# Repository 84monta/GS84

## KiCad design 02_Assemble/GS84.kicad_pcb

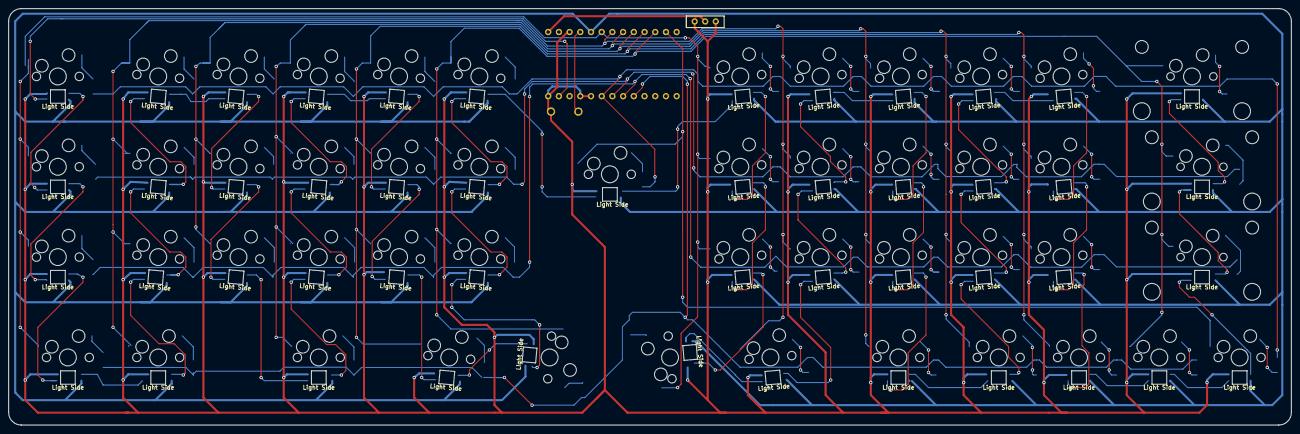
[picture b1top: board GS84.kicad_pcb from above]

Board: 2 copper layers, 304.4 x 98.8 mm, 150 parts (0 on the bottom side), 113 nets.

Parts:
D1, D2, D3, D4, D5, D6, D7, D8, D9, D10, D11, D12, D13, D14, D15, D16, D17, D18, D19, D20, D21, D22, D23, D24, D25, D26, D27, D28, D29, D30, D31, D32, D33, D34, D35, D36, D37, D38, D39, D40, D41, D42, D43, D44, D45, D46, D47, D48, D49: D; Diode_SMD
J1: Conn_01x02; Battery_XH2.5_GL_PCB
L1, L2, L3, L4, L5, L6, L7, L8, L9, L10, L11, L12, L13, L14, L15, L16, L17, L18, L19, L20, L21, L22, L23, L24, L25, L26, L27, L28, L29, L30, L31, L32, L33, L34, L35, L36, L37, L38, L39, L40, L41, L42, L43, L44, L45, L46, L47, L48, L49: SK6812MINI; LED_SK6812MINI-E_BL
SW1, SW2, SW3, SW19, SW23, SW28, SW32: SW_PUSH; CherryMX_Hotswap_1.25u
SW4, SW5, SW6, SW7, SW8, SW9, SW10, SW11, SW12, SW13, SW14, SW15, SW16, SW17, SW18, SW20, SW21, SW22, SW25, SW26, SW27, SW29, SW30, SW31, SW33, SW34, SW35, SW36, SW37, SW38, SW39, SW40, SW41, SW42, SW43, SW44, SW48, SW49: SW_PUSH; CherryMX_Hotswap_1u
SW24: SW_PUSH; CherryMX_Hotswap_1u_Small1
SW45: SW_PUSH; CherryMX_Hotswap_2u
SW46, SW47: SW_PUSH; CherryMX_Hotswap_2.25u
SW50: SW_PUSH; ResetSW
U1: BLEMicroPro; Micon_BMP_GL

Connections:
Bat+: J1.1, U1.25
Col0: SW1.1, SW2.1, SW3.1, SW4.1, SW25.1, SW26.1, SW27.1, SW28.1, U1.20
Col1: SW5.1, SW6.1, SW7.1, SW8.1, SW29.1, SW30.1, SW31.1, SW32.1, U1.19
Col2: SW9.1, SW10.1, SW11.1, SW33.1, SW34.1, SW35.1, SW36.1, U1.18
Col3: SW12.1, SW13.1, SW14.1, SW15.1, SW37.1, SW38.1, SW39.1, SW40.1, U1.17
Col4: SW16.1, SW17.1, SW18.1, SW19.1, SW41.1, SW42.1, SW43.1, SW44.1, U1.16
Col5: SW20.1, SW21.1, SW22.1, SW23.1, SW45.1, SW46.1, SW47.1, SW48.1, U1.15
Col6: SW24.1, SW49.1, U1.14
GND: J1.2, L1.2, L2.2, L3.2, L4.2, L5.2, L6.2, L7.2, L8.2, L9.2, L10.2, L11.2, L12.2, L13.2, L14.2, L15.2, L16.2, L17.2, L18.2, L19.2, L20.2, L21.2, L22.2, L23.2, L24.2, L25.2, L26.2, L27.2, L28.2, L29.2, L30.2, L31.2, L32.2, L33.2, L34.2, L35.2, L36.2, L37.2, L38.2, L39.2, L40.2, L41.2, L42.2, L43.2, L44.2, L45.2, L46.2, L47.2, L48.2, L49.2, SW50.2, U1.3, U1.4, U1.23, U1.26
LED: L1.3, U1.1
unnamed: D1.2, SW1.2
unnamed: D2.2, SW2.2
unnamed: D3.2, SW3.2
unnamed: D4.2, SW4.2
unnamed: D5.2, SW5.2
unnamed: D6.2, SW6.2
unnamed: D7.2, SW7.2
unnamed: D8.2, SW8.2
unnamed: D9.2, SW9.2
unnamed: D10.2, SW10.2
unnamed: D11.2, SW11.2
unnamed: D12.2, SW12.2
unnamed: D13.2, SW13.2
unnamed: D14.2, SW14.2
unnamed: D15.2, SW15.2
unnamed: D16.2, SW16.2
unnamed: D17.2, SW17.2
unnamed: D18.2, SW18.2
unnamed: D19.2, SW19.2
unnamed: D20.2, SW20.2
unnamed: D21.2, SW21.2
unnamed: D22.2, SW22.2
unnamed: D23.2, SW23.2
unnamed: D24.2, SW24.2
unnamed: D25.1, SW25.2
unnamed: D26.1, SW26.2
unnamed: D27.1, SW27.2
unnamed: D28.1, SW28.2
unnamed: D29.1, SW29.2
unnamed: D30.1, SW30.2
unnamed: D31.1, SW31.2
unnamed: D32.1, SW32.2
unnamed: D33.1, SW33.2
unnamed: D34.1, SW34.2
unnamed: D35.1, SW35.2
unnamed: D36.1, SW36.2
unnamed: D37.1, SW37.2
unnamed: D38.1, SW38.2
unnamed: D39.1, SW39.2
unnamed: D40.1, SW40.2
unnamed: D41.1, SW41.2
unnamed: D42.1, SW42.2
unnamed: D43.1, SW43.2
unnamed: D44.1, SW44.2
unnamed: D45.1, SW45.2
unnamed: D46.1, SW46.2
unnamed: D47.1, SW47.2
unnamed: D48.1, SW48.2
unnamed: D49.1, SW49.2
unnamed: L1.1, L2.3
unnamed: L2.1, L3.3
unnamed: L3.1, L4.3
unnamed: L4.1, L5.3
unnamed: L5.1, L6.3
unnamed: L6.1, L7.3
unnamed: L7.1, L8.3
unnamed: L8.1, L9.3
unnamed: L10.1, L11.3
unnamed: L9.1, L10.3
unnamed: L11.1, L12.3
unnamed: L12.1, L13.3
unnamed: L13.1, L14.3
unnamed: L14.1, L15.3
unnamed: L15.1, L16.3
unnamed: L16.1, L17.3
unnamed: L17.1, L18.3
unnamed: L18.1, L19.3
unnamed: L19.1, L20.3
unnamed: L20.1, L21.3
unnamed: L21.1, L22.3
unnamed: L22.1, L23.3
unnamed: L23.1, L24.3
unnamed: L24.1, L25.3
unnamed: L25.1, L26.3
unnamed: L26.1, L27.3
unnamed: L27.1, L28.3
unnamed: L28.1, L29.3
unnamed: L29.1, L30.3
unnamed: L30.1, L31.3
unnamed: L31.1, L32.3
unnamed: L32.1, L33.3
unnamed: L33.1, L34.3
unnamed: L34.1, L35.3
unnamed: L35.1, L36.3
unnamed: L36.1, L37.3
unnamed: L37.1, L38.3
unnamed: L38.1, L39.3
unnamed: L39.1, L40.3
unnamed: L40.1, L41.3
unnamed: L41.1, L42.3
unnamed: L42.1, L43.3
unnamed: L43.1, L44.3
unnamed: L44.1, L45.3
unnamed: L45.1, L46.3
unnamed: L46.1, L47.3
unnamed: L47.1, L48.3
unnamed: L48.1, L49.3
Reset: SW50.1, U1.22
Row0: D1.1, D5.1, D9.1, D12.1, D16.1, D20.1, D24.1, D25.2, D29.2, D33.2, D37.2, D41.2, D45.2, D49.2, U1.5
Row1: D2.1, D6.1, D10.1, D13.1, D17.1, D21.1, D26.2, D30.2, D34.2, D38.2, D42.2, D46.2, U1.6
Row2: D3.1, D7.1, D11.1, D14.1, D18.1, D22.1, D27.2, D31.2, D35.2, D39.2, D43.2, D47.2, U1.7
Row3: D4.1, D8.1, D15.1, D19.1, D23.1, D28.2, D32.2, D36.2, D40.2, D44.2, D48.2, U1.8
VCC: L1.4, L2.4, L3.4, L4.4, L5.4, L6.4, L7.4, L8.4, L9.4, L10.4, L11.4, L12.4, L13.4, L14.4, L15.4, L16.4, L17.4, L18.4, L19.4, L20.4, L21.4, L22.4, L23.4, L24.4, L25.4, L26.4, L27.4, L28.4, L29.4, L30.4, L31.4, L32.4, L33.4, L34.4, L35.4, L36.4, L37.4, L38.4, L39.4, L40.4, L41.4, L42.4, L43.4, L44.4, L45.4, L46.4, L47.4, L48.4, L49.4, U1.21

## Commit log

2022-01-16 Initial Version
2022-01-21 レビューいただいた内容を反映
    ProMicoroを中央に移動、ダイオードを表面実装だけに修正、バッテリーホールと信号線の距離を広げる
